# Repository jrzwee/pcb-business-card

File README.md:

# pcb-business-card
PCB business card with personal contact data

## Usage
This PCB should be manufactured in 0.6 mm or 0.8 mm.

## Renders
[comment]: 
[comment]: 

## License
[CERN-OHL-S](https://ohwr.org/cern_ohl_s_v2.pdf)

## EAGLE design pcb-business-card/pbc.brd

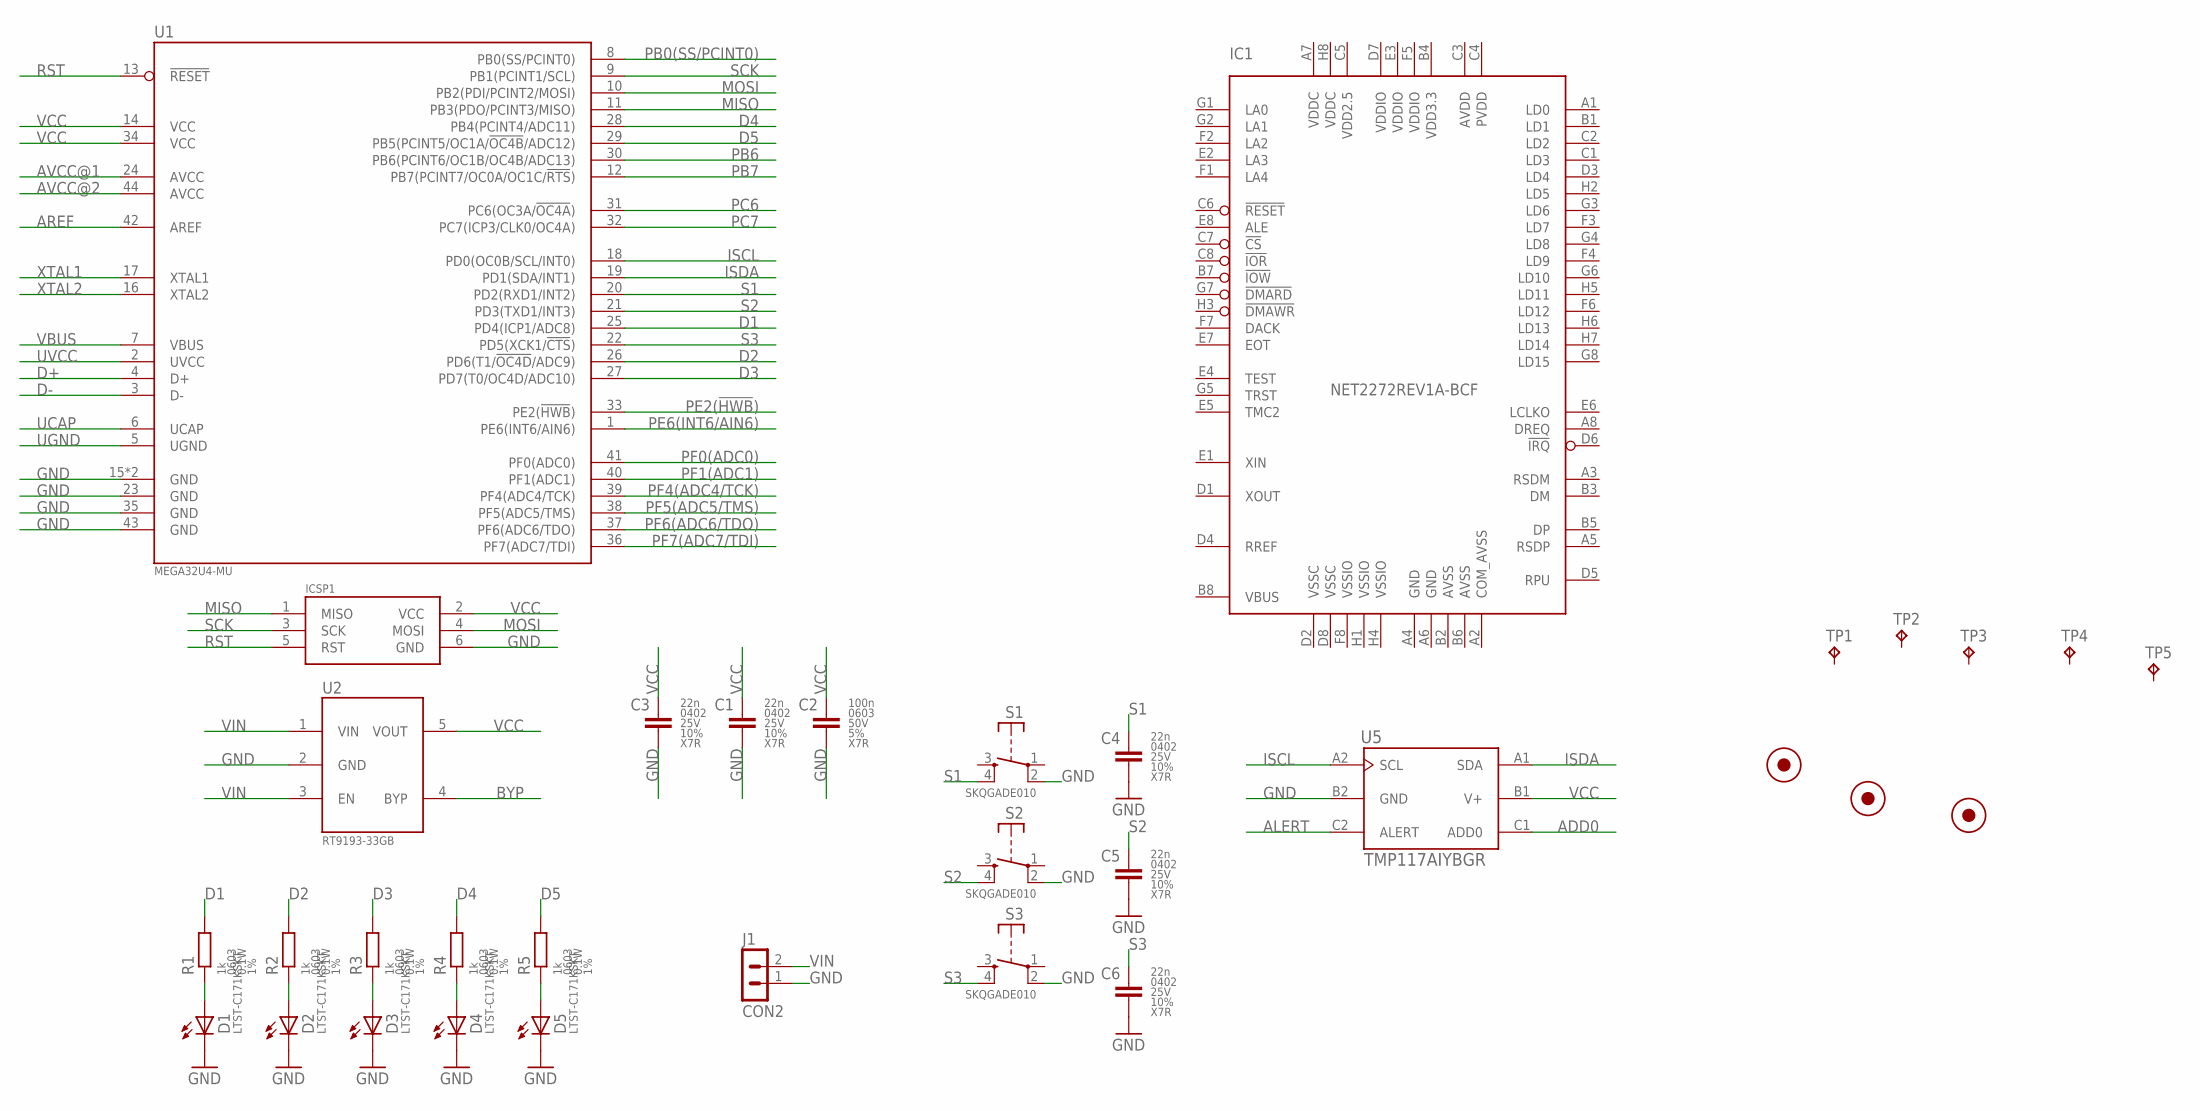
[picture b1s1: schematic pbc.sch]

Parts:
C1, C3, C4, C5, C6: 22n; C0402
C2: 100n; C0603
D1, D2, D3, D4, D5: LTST-C171KSKT; CHIPLED_0805
FD1, FD2, FD3: FIDUCIAL; FIDUCIAL_1MM
IC1: NET2272REV1A-BCF; FBGA64
ICSP1: AVR-ISP-SKEDD; 490107670612_DEBUGGING
J1: CON2; H2-2.54
R1, R2, R3, R4, R5: 1k; R0603
S1, S2, S3: SKQGADE010; TACTILE_SWITCH_SMD_5.2MM
TP1, TP2, TP3, TP4, TP5: TP-B0.635; B0.635
U1: MEGA32U4-MU; TQFN44_7MM
U2: RT9193-33GB; SOT23-5
U5: TMP117AIYBGR

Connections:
ADD0: U5.C1 (ADD0)
ALERT: U5.C2 (ALERT)
AREF: U1.42 (AREF)
AVCC@1: U1.24 (AVCC)
AVCC@2: U1.44 (AVCC)
AVDD: IC1.C3 (AVDD)
AVSS: IC1.B2 (AVSS), IC1.B6 (AVSS)
BYP: U2.4 (BYP)
COM_AVSS: IC1.A2 (COM_AVSS)
D1: R1.2, U1.25 (PD4(ICP1/ADC8))
D2: R2.2, U1.26 (PD6(T1/!OC4D!/ADC9))
D3: R3.2, U1.27 (PD7(T0/OC4D/ADC10))
D4: R4.2, U1.28 (PB4(PCINT4/ADC11))
D5: R5.2, U1.29 (PB5(PCINT5/OC1A/!OC4B!/ADC12))
D+: U1.4 (D+)
D-: U1.3 (D-)
GND: C1.2, C2.2, C3.2, C4.2, C5.2, C6.2, D1.C, D2.C, D3.C, D4.C, D5.C, IC1.A4 (GND), IC1.A6 (GND), ICSP1.6 (GND), J1.1, S1.2, S2.2, S3.2, U1.15 (GND), U1.23 (GND), U1.35 (GND), U1.43 (GND), U1.EXP (GND), U2.2 (GND), U5.B2 (GND)
ISCL: U1.18 (PD0(OC0B/SCL/INT0)), U5.A2 (SCL)
ISDA: U1.19 (PD1(SDA/INT1)), U5.A1 (SDA)
MISO: ICSP1.1 (MISO), U1.11 (PB3(PDO/PCINT3/MISO))
MOSI: ICSP1.4 (MOSI), U1.10 (PB2(PDI/PCINT2/MOSI))
unnamed: D1.A, R1.1
unnamed: D2.A, R2.1
unnamed: D3.A, R3.1
unnamed: D4.A, R4.1
unnamed: D5.A, R5.1
PB0(SS/PCINT0): U1.8 (PB0(SS/PCINT0))
PB6: U1.30 (PB6(PCINT6/OC1B/OC4B/ADC13))
PB7: U1.12 (PB7(PCINT7/OC0A/OC1C/!RTS!))
PC6: U1.31 (PC6(OC3A/!OC4A!))
PC7: U1.32 (PC7(ICP3/CLK0/OC4A))
PE2(!HWB!): U1.33 (PE2(!HWB!))
PE6(INT6/AIN6): U1.1 (PE6(INT6/AIN6))
PF0(ADC0): U1.41 (PF0(ADC0))
PF1(ADC1): U1.40 (PF1(ADC1))
PF4(ADC4/TCK): U1.39 (PF4(ADC4/TCK))
PF5(ADC5/TMS): U1.38 (PF5(ADC5/TMS))
PF6(ADC6/TDO): U1.37 (PF6(ADC6/TDO))
PF7(ADC7/TDI): U1.36 (PF7(ADC7/TDI))
PVDD: IC1.C4 (PVDD)
RST: ICSP1.5 (RST), U1.13 (!RESET!)
S1: C4.1, S1.4 (S), U1.20 (PD2(RXD1/INT2))
S2: C5.1, S2.4 (S), U1.21 (PD3(TXD1/INT3))
S3: C6.1, S3.4 (S), U1.22 (PD5(XCK1/!CTS!))
SCK: ICSP1.3 (SCK), U1.9 (PB1(PCINT1/SCL))
UCAP: U1.6 (UCAP)
UGND: U1.5 (UGND)
UVCC: U1.2 (UVCC)
VBUS: U1.7 (VBUS)
VCC: C1.1, C2.1, C3.1, ICSP1.2 (VCC), U1.14 (VCC), U1.34 (VCC), U2.5 (VOUT), U5.B1 (V+)
VDD2.5: IC1.C5 (VDD2.5)
VDD3.3: IC1.B4 (VDD3.3)
VDDC: IC1.A7 (VDDC), IC1.H8 (VDDC)
VDDIO: IC1.D7 (VDDIO), IC1.E3 (VDDIO), IC1.F5 (VDDIO)
VIN: J1.2, U2.1 (VIN), U2.3 (EN)
VSSC: IC1.D2 (VSSC), IC1.D8 (VSSC)
VSSIO: IC1.F8 (VSSIO), IC1.H1 (VSSIO), IC1.H4 (VSSIO)
XTAL1: U1.17 (XTAL1)
XTAL2: U1.16 (XTAL2)

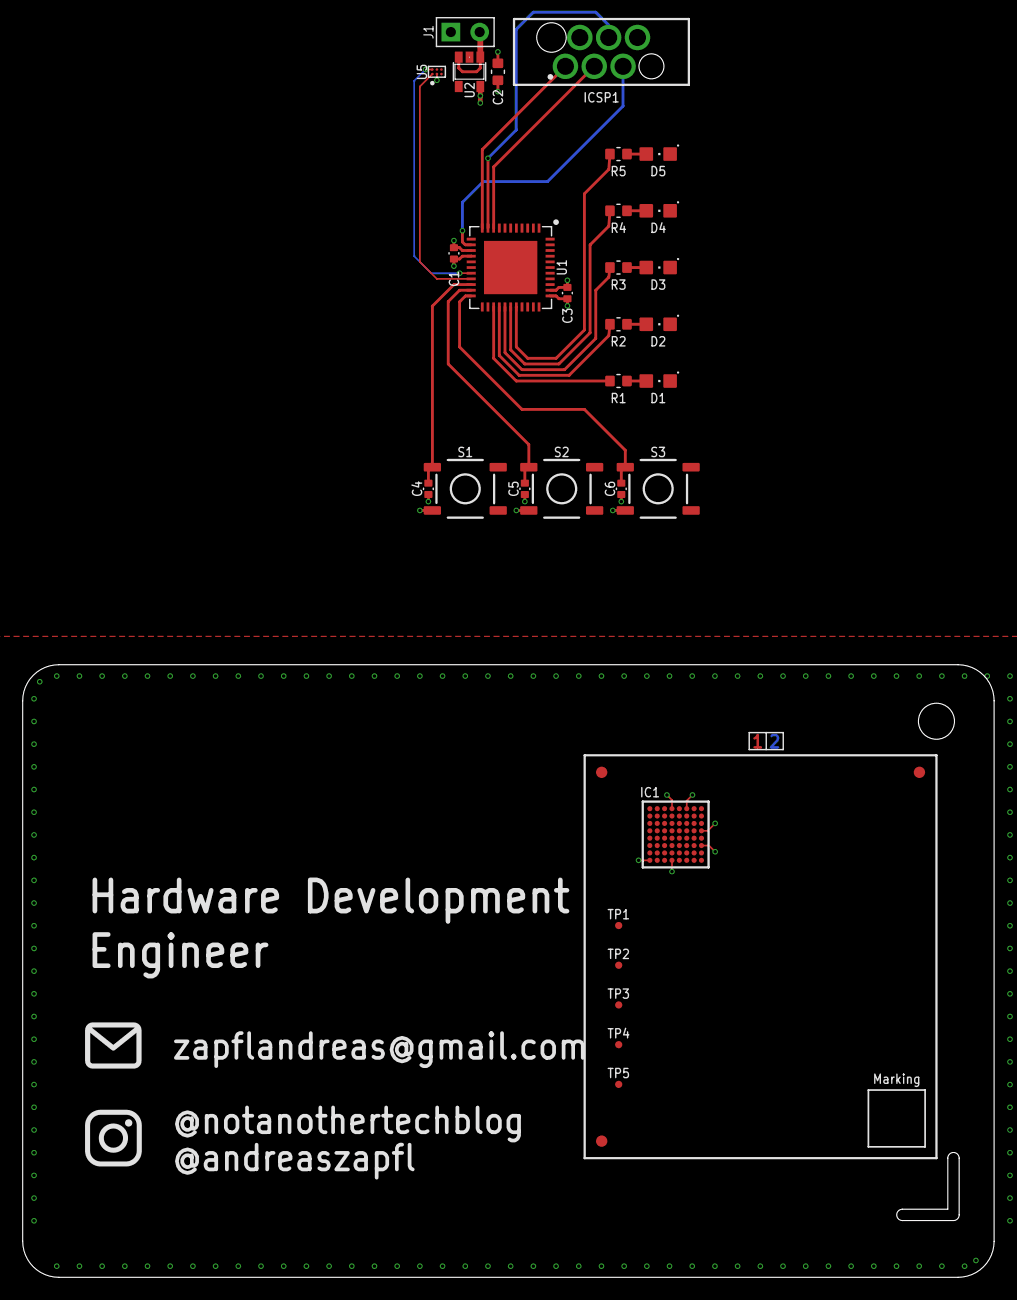
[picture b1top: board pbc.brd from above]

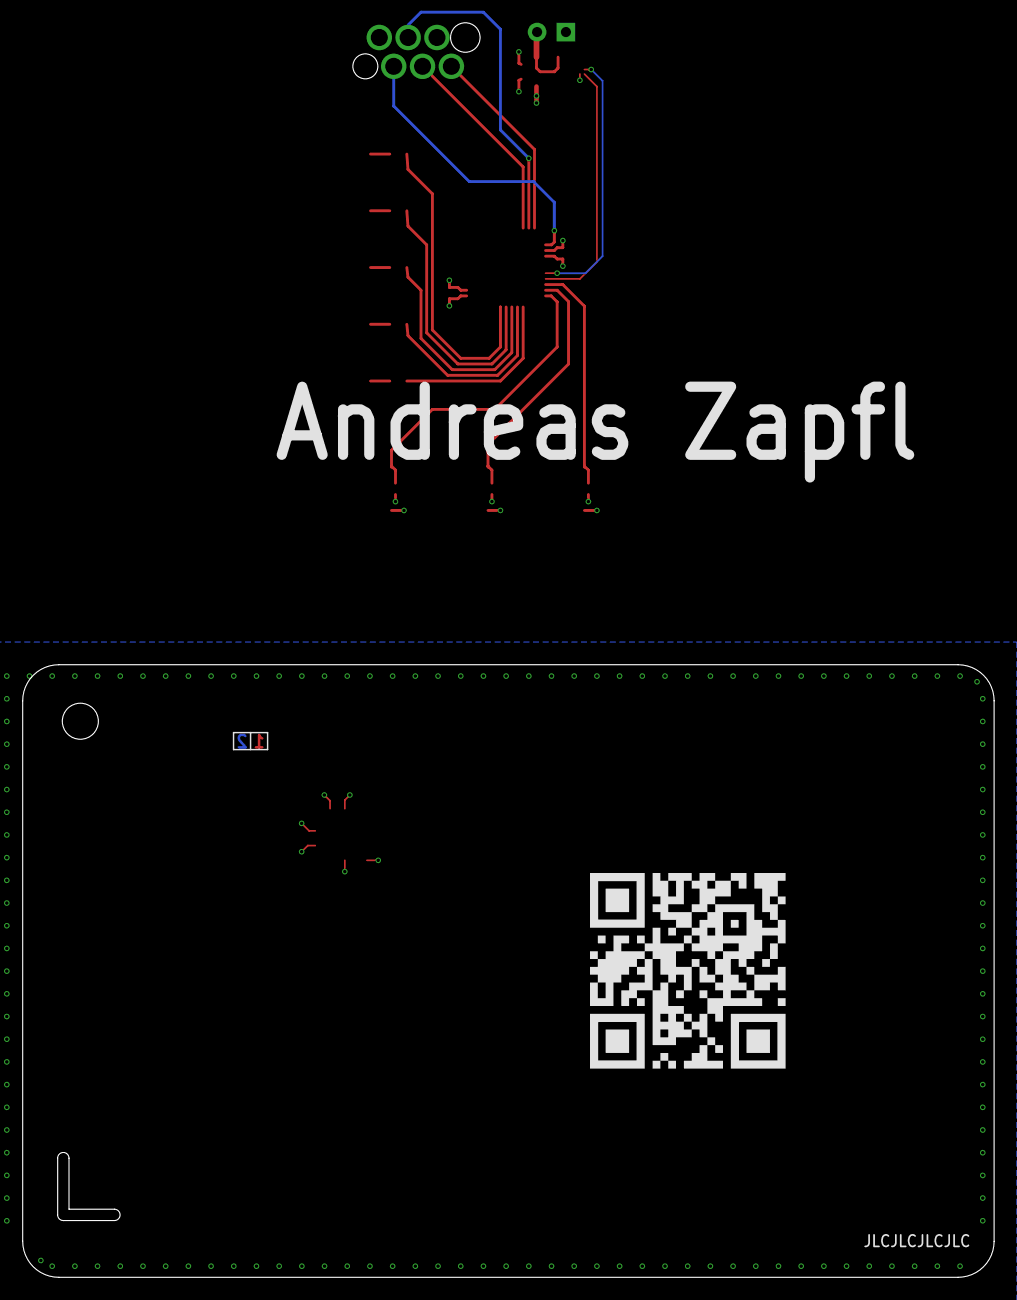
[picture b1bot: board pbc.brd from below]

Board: 2 copper layers, 85.6 x 54.0 mm, 39 parts (2 on the bottom side), 27 nets.

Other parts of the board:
U$1: JLC_UID
U$2: INSTA-5
U$3: MAIL-5
U$4: GITHUB-JRZ-20
U$5: STACKUP-2L
U$6: QR-SPACE

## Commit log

2021-01-24 Initial try
2021-01-24 Added instagram and mail logo
2021-01-24 Created gerbers
2021-01-24 Changed folder structure
2021-01-24 Create LICENSE
2021-01-27 Black substrate change
2021-01-27 Deleted whitespace in "hardware development"
2021-01-27 Deleted unused layers
2021-03-12 Resized renders in Readme
2021-09-13 Updated format to id-1 size
2021-09-16 Working on verion 2
2021-09-16 Working on version 2
2021-09-16 Added TP and FID

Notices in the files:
parts and their libraries:
plxtech: PCI 9056 Data Book, Version 0.91© 2001 PLX Technology, Inc.
All rights reserved.
